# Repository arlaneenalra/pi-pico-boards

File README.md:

# pi-pico-boards
A place to keep various pi-pico-board experiments

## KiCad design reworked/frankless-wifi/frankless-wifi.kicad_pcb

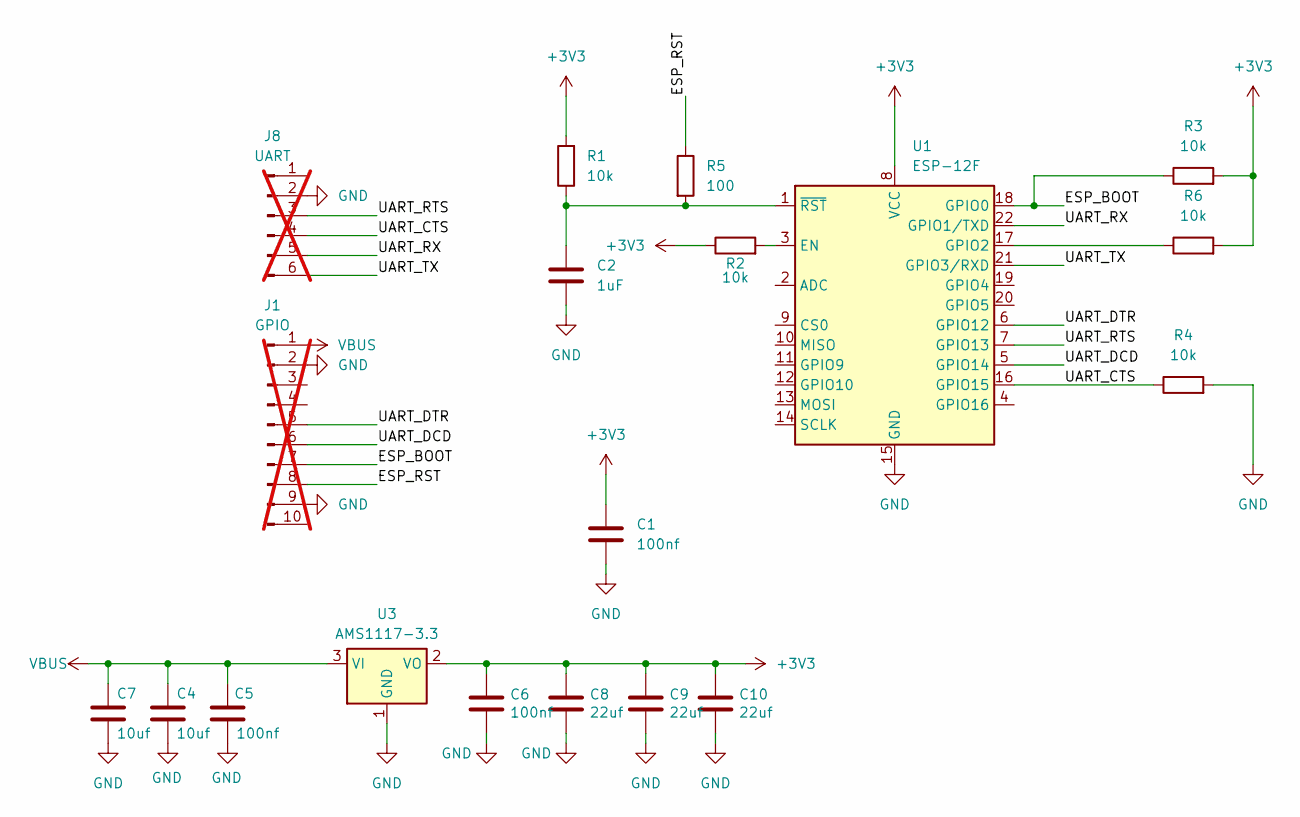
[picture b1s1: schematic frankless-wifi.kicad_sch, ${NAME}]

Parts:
C1: 100nf; C_0402_1005Metric; LCSC C1525
C2: 1uF; C_0402_1005Metric; LCSC C52923
C4, C7: 10uf; C_0603_1608Metric; LCSC Part # C96446
C5, C6: 100nf; C_0402_1005Metric; LCSC Part # C1525
C8, C9, C10: 22uf; C_0603_1608Metric; LCSC Part # C59461
J1: GPIO; PinHeader_2x05_P2.54mm_Vertical; not fitted
J8: UART; PinHeader_2x03_P2.54mm_Vertical; not fitted
R1, R2, R3, R4, R6: 10k; R_0402_1005Metric; LCSC C25744
R5: 100; R_0402_1005Metric; LCSC C25076
U1: ESP-12F; ESP-12E
U3: AMS1117-3.3; SOT-223-3_TabPin2; LCSC Part # C6186

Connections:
+3V3: C1.1, C6.1, C8.1, C9.1, C10.1, R1.2, R2.1, R3.2, R6.2, U1.8 (VCC), U3.2 (VO)
/ESP_BOOT: J1.7, R3.1, U1.18 (GPIO0)
/ESP_RST: J1.8, R5.1
/UART_CTS: J8.4, R4.1, U1.16 (GPIO15)
/UART_DCD: J1.6, U1.5 (GPIO14)
/UART_DTR: J1.5, U1.6 (GPIO12)
/UART_RTS: J8.3, U1.7 (GPIO13)
/UART_RX: J8.5, U1.22 (GPIO1/TXD)
/UART_TX: J8.6, U1.21 (GPIO3/RXD)
GND: C1.2, C2.2, C4.1, C5.1, C6.2, C7.1, C8.2, C9.2, C10.2, J1.2, J1.9, J8.2, R4.2, U1.15 (GND), U3.1 (GND)
unnamed: R2.2, U1.3 (EN)
unnamed: R6.1, U1.17 (GPIO2)
unnamed: C2.1, R1.1, R5.2, U1.1 (~RST)
VBUS: C4.2, C5.2, C7.2, J1.1, U3.3 (VI)

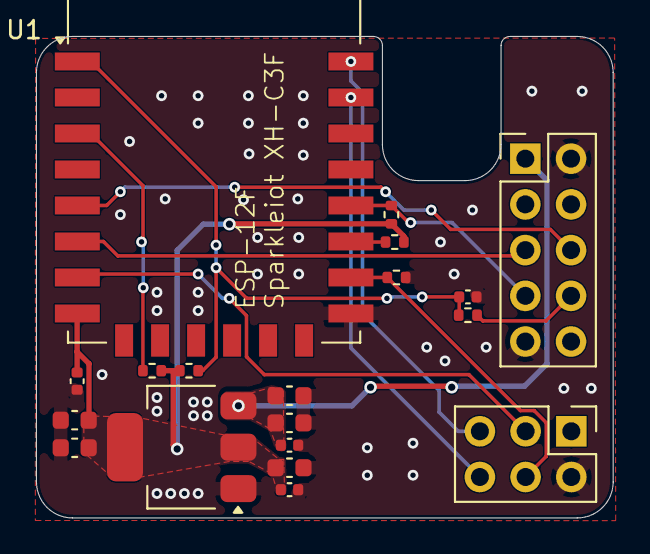
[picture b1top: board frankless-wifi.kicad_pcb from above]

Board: 2 copper layers, 32.0 x 26.8 mm, 19 parts (0 on the bottom side), 14 nets.

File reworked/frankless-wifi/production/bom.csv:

Designator,Footprint,Quantity,Value,LCSC Part #
"C1, C5, C6",0402,3,100nf,C1525
"C10, C8, C9",0603,3,22uf,C59461
C2,0402,1,1uF,C52923
"C4, C7",0603,2,10uf,C96446
"R1, R2, R3, R4, R6",0402,5,10k,C25744
R5,0402,1,100,C25076
U3,SOT-223-3_TabPin2,1,AMS1117-3.3,C6186

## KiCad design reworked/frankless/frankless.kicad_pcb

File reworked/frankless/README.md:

This is a reworked version of rh1tech's [MicroFrank](https://github.com/rh1tech/frank/tree/master/hardware/microfrank) board. I wound up stripping it down to the basically a bare PCB and reworking the layout almost from scratch. The USB Hub and several other components have been switched out to account for what JLCPCB can provide.

As the original is GPL V3, I'll license this board in particular GPL V3 as well.

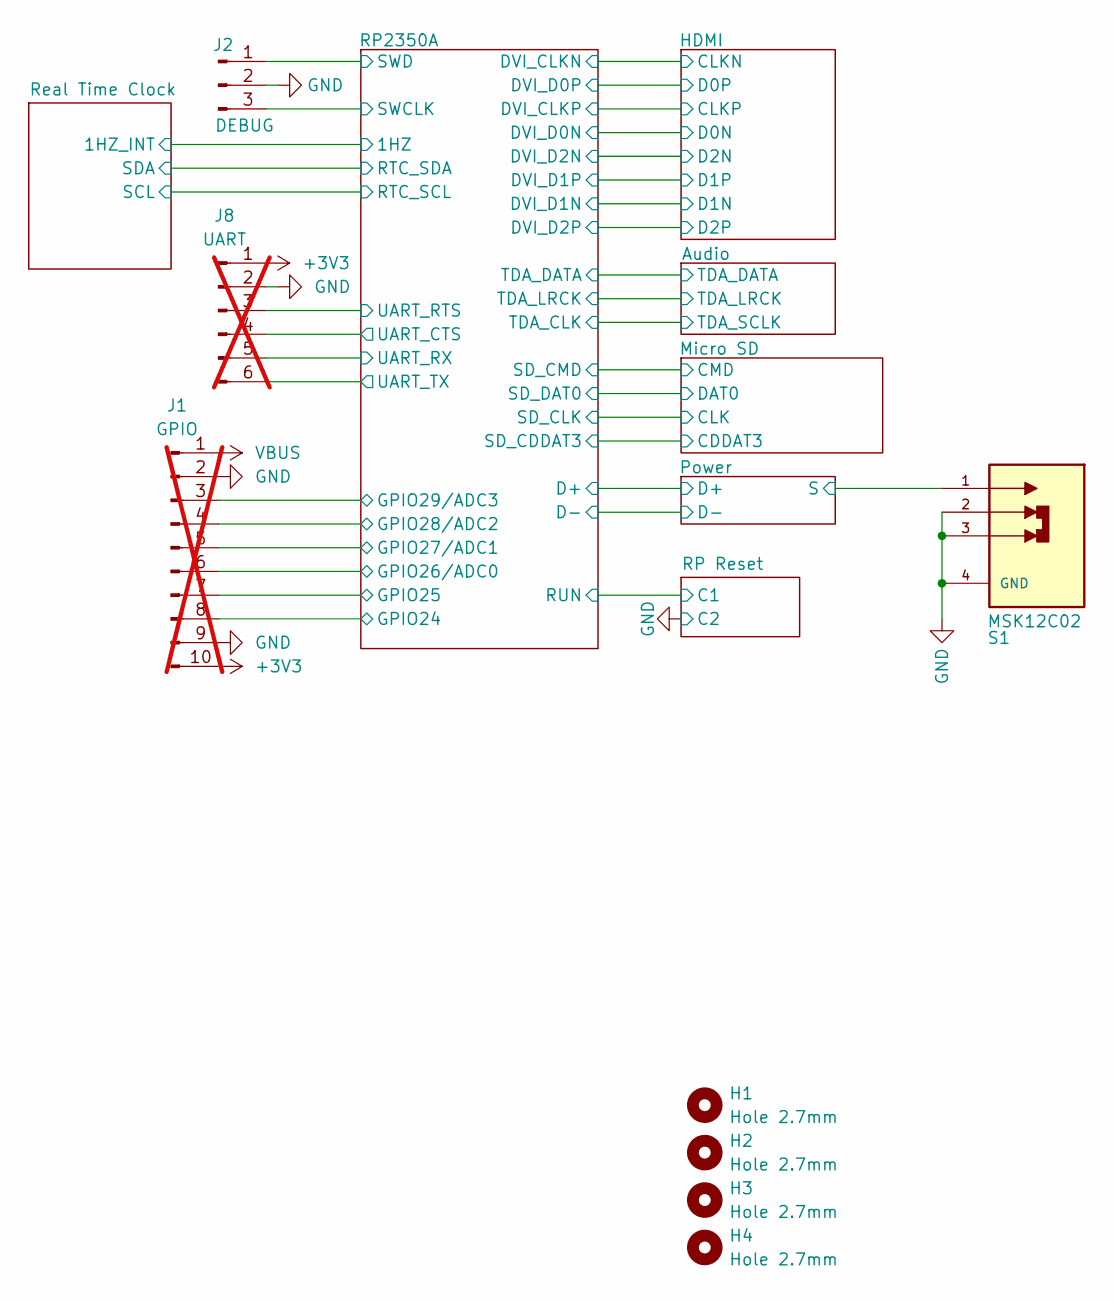
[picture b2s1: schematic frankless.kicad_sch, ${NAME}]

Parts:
H1, H2, H3, H4: Hole 2.7mm; MountingHole_2.7mm
J1: GPIO; PinHeader_2x05_P2.54mm_Vertical; not fitted
J2: DEBUG; JST_SH_1x03_P1.00mm_Vertical; LCSC Part # C160389
J8: UART; PinHeader_2x03_P2.54mm_Vertical; not fitted
S1: MSK12C02; Switch_Slide_MSK12C02; PARTREV A/0; LCSC Part # C431540

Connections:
+3V3: J1.10, J8.1; also elsewhere on the board
/Power/S: S1.1; also elsewhere on the board
/RP2350A/GPIO24: J1.8; also elsewhere on the board
/RP2350A/GPIO25: J1.7; also elsewhere on the board
/RP2350A/GPIO26/ADC0: J1.6; also elsewhere on the board
/RP2350A/GPIO27/ADC1: J1.5; also elsewhere on the board
/RP2350A/GPIO28/ADC2: J1.4; also elsewhere on the board
/RP2350A/GPIO29/ADC3: J1.3; also elsewhere on the board
/RP2350A/SWCLK: J2.3; also elsewhere on the board
/RP2350A/SWD: J2.1; also elsewhere on the board
/RP2350A/UART_CTS: J8.4; also elsewhere on the board
/RP2350A/UART_RTS: J8.3; also elsewhere on the board
/RP2350A/UART_RX: J8.5; also elsewhere on the board
/RP2350A/UART_TX: J8.6; also elsewhere on the board
GND: J1.2, J1.9, J2.2, J8.2, S1.2, S1.3, S1.4 (GND_4); also elsewhere on the board
VBUS: J1.1; also elsewhere on the board

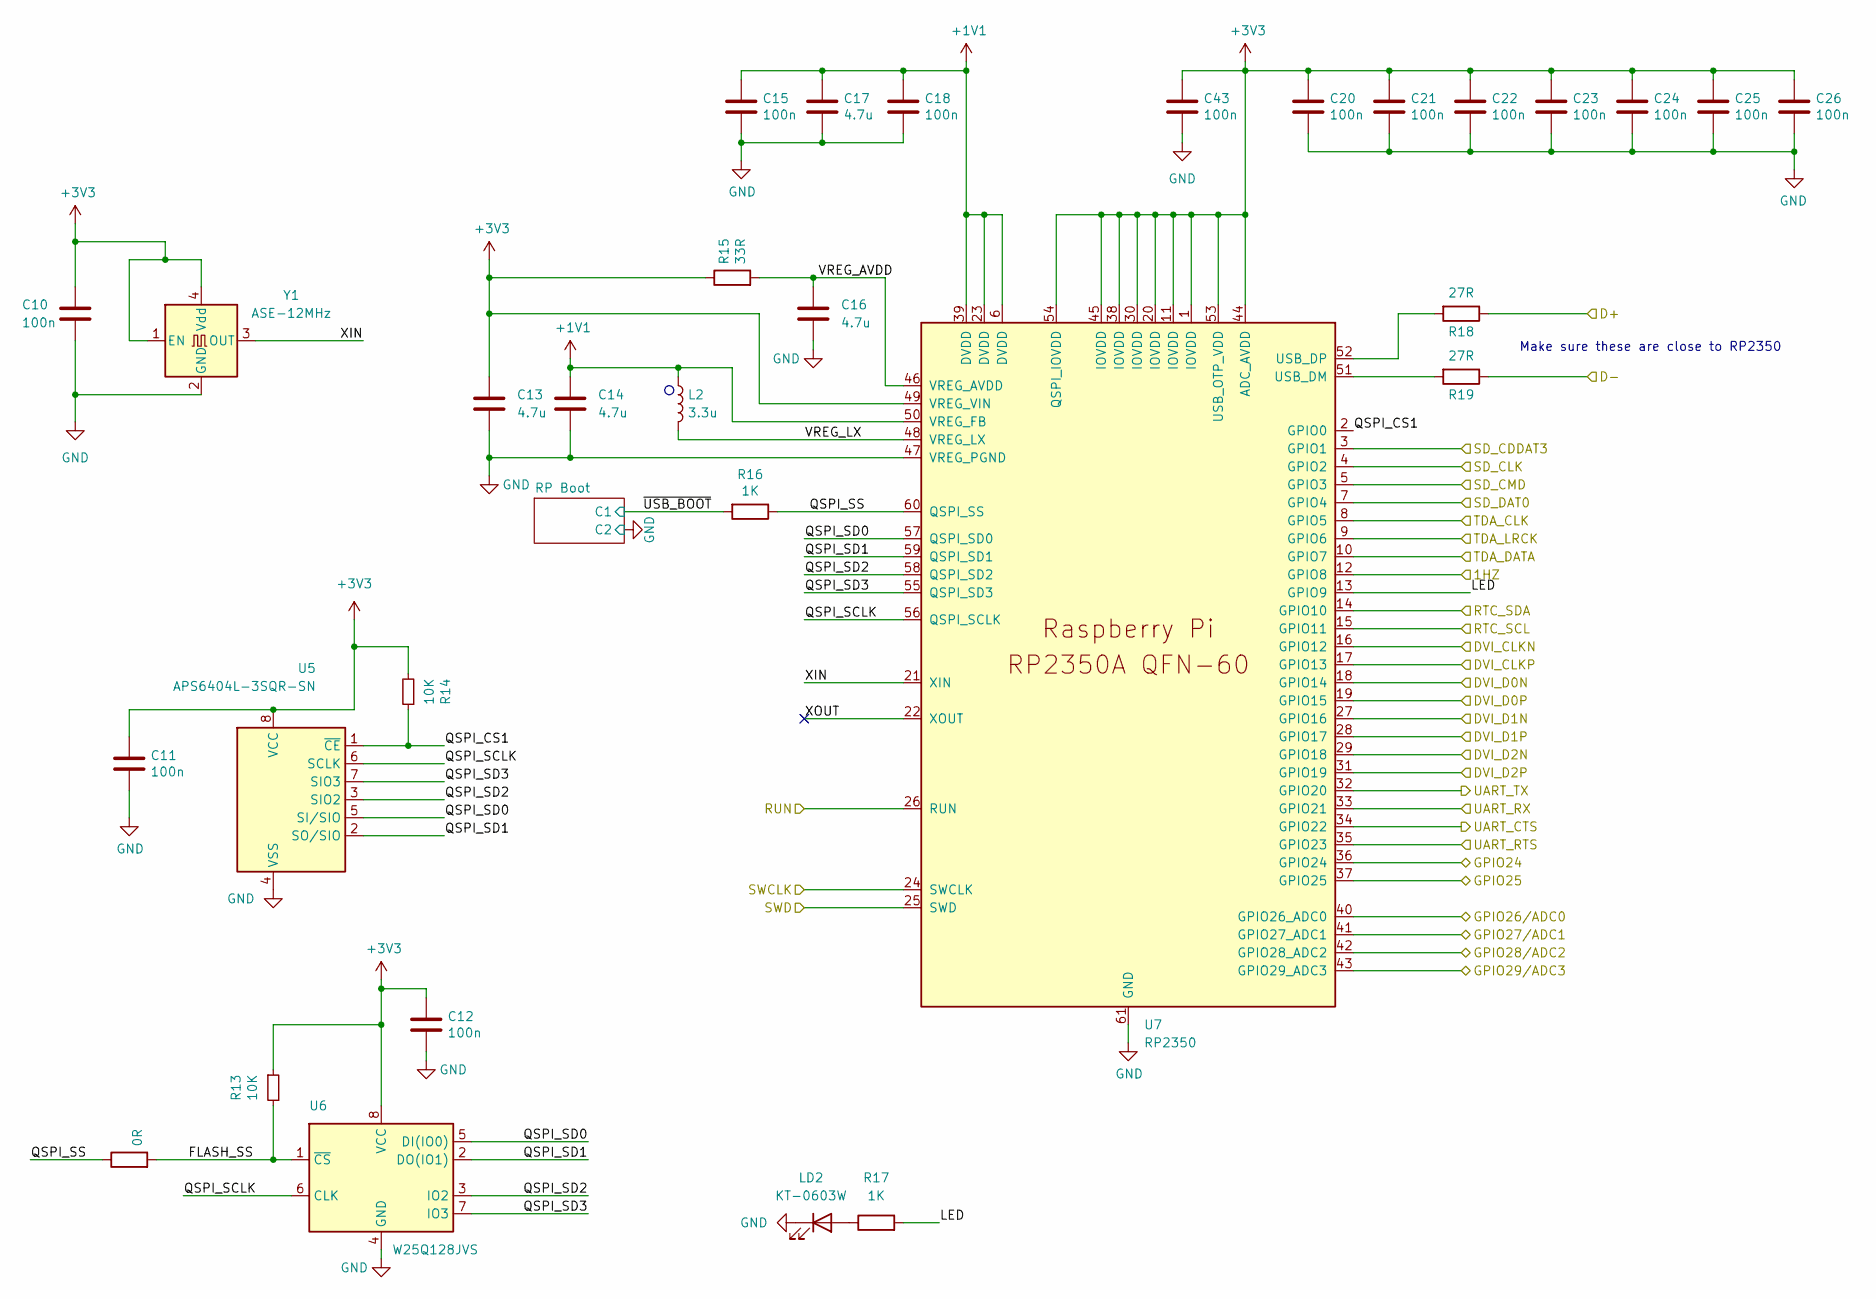
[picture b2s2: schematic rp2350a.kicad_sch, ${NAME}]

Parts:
C10, C11, C12, C15, C18, C20, C21, C22, C23, C24, C25, C26, C43: 100n; C_0402_1005Metric; LCSC Part # C1525
C13, C14: 4.7u; C_0603_1608Metric; LCSC Part # C19666
C16, C17: 4.7u; C_0402_1005Metric; LCSC Part # C2986286
L2: 3.3u; AOTA-B201610S3R3-101-T; LCSC Part # C42411119
LD2: KT-0603W; LED_0603_1608Metric; LCSC Part # C2290
R12: 0R; R_0402_1005Metric; LCSC Part # C17168
R13, R14: 10K; R_0402_1005Metric; LCSC Part # C25744
R15: 33R; R_0402_1005Metric; LCSC Part # C25105
R16, R17: 1K; R_0402_1005Metric; LCSC Part # C11702
R18, R19: 27R; R_0201_0603Metric; LCSC Part # C473051
U5: APS6404L-3SQR-SN; SOIC-8_L4.9-W3.9-P1.27-LS6.0-BL; LCSC Part # C5333729
U6: W25Q128JVS; SOIC-8; LCSC Part # C97521
U7: RP2350; QFN-60_RP2350A; LCSC Part # C42411118
Y1: ASE-12MHz; OSC-SMD_4P-L1.6-W1.2-BL; LCSC Part # C20539386

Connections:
+1V1: C14.1, C15.1, C17.1, C18.1, L2.1, U7.6 (DVDD), U7.23 (DVDD), U7.39 (DVDD), U7.50 (VREG_FB)
+3V3: C10.1, C11.1, C12.1, C13.1, C20.1, C21.1, C22.1, C23.1, C24.1, C25.1, C26.1, C43.1, R13.1, R14.2, R15.1, U5.8 (VCC), U6.8 (VCC), U7.1 (IOVDD), U7.11 (IOVDD), U7.20 (IOVDD), U7.30 (IOVDD), U7.38 (IOVDD), U7.44 (ADC_AVDD), U7.45 (IOVDD), U7.49 (VREG_VIN), U7.53 (USB_OTP_VDD), U7.54 (QSPI_IOVDD), Y1.1 (EN), Y1.4 (Vdd); also elsewhere on the board
/Audio/TDA_DATA: U7.10 (GPIO7); also elsewhere on the board
/Audio/TDA_LRCK: U7.9 (GPIO6); also elsewhere on the board
/Audio/TDA_SCLK: U7.8 (GPIO5); also elsewhere on the board
/HDMI/CLKN: U7.16 (GPIO12); also elsewhere on the board
/HDMI/CLKP: U7.17 (GPIO13); also elsewhere on the board
/HDMI/D0N: U7.18 (GPIO14); also elsewhere on the board
/HDMI/D0P: U7.19 (GPIO15); also elsewhere on the board
/HDMI/D1N: U7.27 (GPIO16); also elsewhere on the board
/HDMI/D1P: U7.28 (GPIO17); also elsewhere on the board
/HDMI/D2N: U7.29 (GPIO18); also elsewhere on the board
/HDMI/D2P: U7.31 (GPIO19); also elsewhere on the board
/Micro SD/CDDAT3: U7.3 (GPIO1); also elsewhere on the board
/Micro SD/CLK: U7.4 (GPIO2); also elsewhere on the board
/Micro SD/CMD: U7.5 (GPIO3); also elsewhere on the board
/Micro SD/DAT0: U7.7 (GPIO4); also elsewhere on the board
/Power/D+: R18.1; also elsewhere on the board
/Power/D-: R19.1; also elsewhere on the board
/RP2350A/1HZ: U7.12 (GPIO8); also elsewhere on the board
/RP2350A/FLASH_SS: R12.2, R13.2, U6.1 (~CS)
/RP2350A/GPIO24: U7.36 (GPIO24); also elsewhere on the board
/RP2350A/GPIO25: U7.37 (GPIO25); also elsewhere on the board
/RP2350A/GPIO26/ADC0: U7.40 (GPIO26_ADC0); also elsewhere on the board
/RP2350A/GPIO27/ADC1: U7.41 (GPIO27_ADC1); also elsewhere on the board
/RP2350A/GPIO28/ADC2: U7.42 (GPIO28_ADC2); also elsewhere on the board
/RP2350A/GPIO29/ADC3: U7.43 (GPIO29_ADC3); also elsewhere on the board
/RP2350A/LED: R17.2, U7.13 (GPIO9)
/RP2350A/QSPI_CS1: R14.1, U5.1 (~CE), U7.2 (GPIO0)
/RP2350A/QSPI_SCLK: U5.6 (SCLK), U6.6 (CLK), U7.56 (QSPI_SCLK)
/RP2350A/QSPI_SD0: U5.5 (SI/SIO), U6.5 (DI(IO0)), U7.57 (QSPI_SD0)
/RP2350A/QSPI_SD1: U5.2 (SO/SIO), U6.2 (DO(IO1)), U7.59 (QSPI_SD1)
/RP2350A/QSPI_SD2: U5.3 (SIO2), U6.3 (IO2), U7.58 (QSPI_SD2)
/RP2350A/QSPI_SD3: U5.7 (SIO3), U6.7 (IO3), U7.55 (QSPI_SD3)
/RP2350A/QSPI_SS: R12.1, R16.1, U7.60 (QSPI_SS)
/RP2350A/RTC_SCL: U7.15 (GPIO11); also elsewhere on the board
/RP2350A/RTC_SDA: U7.14 (GPIO10); also elsewhere on the board
/RP2350A/SWCLK: U7.24 (SWCLK); also elsewhere on the board
/RP2350A/SWD: U7.25 (SWD); also elsewhere on the board
/RP2350A/UART_CTS: U7.34 (GPIO22); also elsewhere on the board
/RP2350A/UART_RTS: U7.35 (GPIO23); also elsewhere on the board
/RP2350A/UART_RX: U7.33 (GPIO21); also elsewhere on the board
/RP2350A/UART_TX: U7.32 (GPIO20); also elsewhere on the board
/RP2350A/VREG_AVDD: C16.1, R15.2, U7.46 (VREG_AVDD)
/RP2350A/VREG_LX: L2.2, U7.48 (VREG_LX)
/RP2350A/XIN: U7.21 (XIN), Y1.3 (OUT)
/RP2350A/XOUT: U7.22 (XOUT)
/RP2350A/~USB_BOOT: R16.2; also elsewhere on the board
/RP Reset/C1: U7.26 (RUN); also elsewhere on the board
GND: C10.2, C11.2, C12.2, C13.2, C14.2, C15.2, C16.2, C17.2, C18.2, C20.2, C21.2, C22.2, C23.2, C24.2, C25.2, C26.2, C43.2, LD2.1 (K), U5.4 (VSS), U6.4 (GND), U7.47 (VREG_PGND), U7.61 (GND), Y1.2 (GND); also elsewhere on the board
unnamed: LD2.2 (A), R17.1
unnamed: R19.2, U7.51 (USB_DM)
unnamed: R18.2, U7.52 (USB_DP)

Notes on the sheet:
Make sure these are close to RP2350

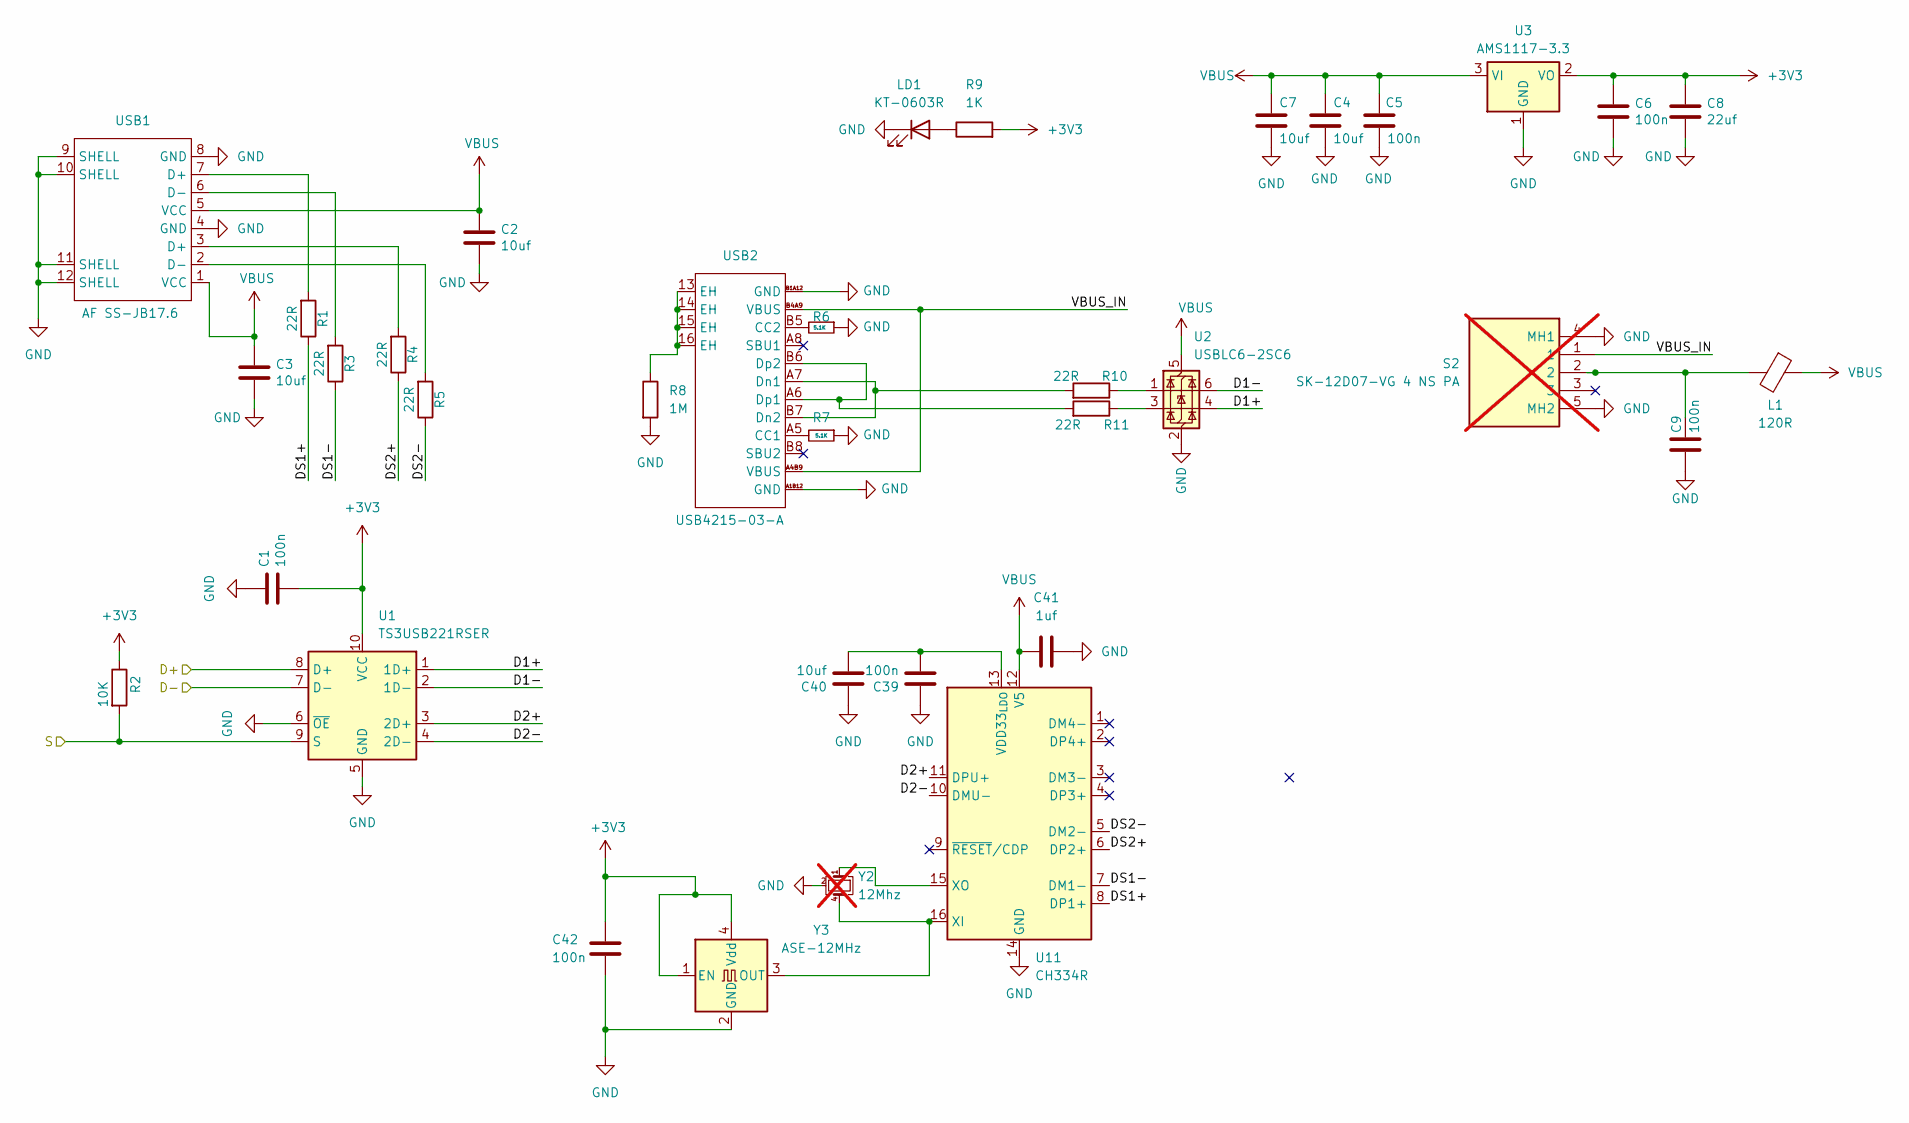
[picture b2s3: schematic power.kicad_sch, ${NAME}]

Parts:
C1, C5, C6, C9, C39, C42: 100n; C_0402_1005Metric; LCSC Part # C1525
C2, C3, C40: 10uf; C_0402_1005Metric; LCSC Part # C77000
C4, C7: 10uf; C_0603_1608Metric; LCSC Part # C96446
C8: 22uf; C_0603_1608Metric; LCSC Part # C59461
C41: 1uf; C_0402_1005Metric; LCSC Part # C14445
L1: 120R; L_0603_1608Metric; LCSC Part # C14709
LD1: KT-0603R; LED_0603_1608Metric; LCSC Part # C2286
R1, R3, R4, R5, R10, R11: 22R; R_0402_1005Metric; LCSC Part # C25092
R2: 10K; R_0402_1005Metric; LCSC Part # C25744
R6, R7: 5.1K; R_0402_1005Metric; LCSC Part # C25905
R8: 1M; R_0402_1005Metric; LCSC Part # C26083
R9: 1K; R_0402_1005Metric; LCSC Part # C11702
S2: SK-12D07-VG 4 NS PA; Switch_Slide_SK12D07VG3NS; Mouser Part Number 611-SK12D07VG3NS; not fitted
U1: TS3USB221RSER; UQFN-10; LCSC Part # C130085
U2: USBLC6-2SC6; SOT-23-6; LCSC Part # C2687116
U3: AMS1117-3.3; SOT-223-3_TabPin2; LCSC Part # C6186
U11: CH334R; QSOP-16_3.9x4.9mm_P0.635mm; LCSC Part # C4154405
USB1: AF SS-JB17.6; USB-A-TH_AF-SS-JB17.6; Manufacturer Part AF SS-JB17.6; LCSC Part Name Type-A 母 弯插
USB2: USB4215-03-A; USB-C-SMD_GT-USB-7010B; Manufacturer Part USB4215-03-A; LCSC Part Name Type-C 母
Y2: 12Mhz; CRYSTAL-SMD_4P-L3.2-W2.5-BL; LCSC Part # C9002; not fitted
Y3: ASE-12MHz; OSC-SMD_4P-L1.6-W1.2-BL; LCSC Part # C20539386

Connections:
+3V3: C1.2, C6.1, C8.1, C42.1, R2.1, R9.2, U1.10 (VCC), U3.2 (VO), Y3.1 (EN), Y3.4 (Vdd); also elsewhere on the board
/Power/D1+: U1.1 (1D+), U2.4 (I/O2)
/Power/D1-: U1.2 (1D-), U2.6 (I/O1)
/Power/D2+: U1.3 (2D+), U11.11 (DPU+)
/Power/D2-: U1.4 (2D-), U11.10 (DMU-)
/Power/D+: U1.8 (D+); also elsewhere on the board
/Power/D-: U1.7 (D-); also elsewhere on the board
/Power/DS1+: R1.1, U11.8 (DP1+)
/Power/DS1-: R3.1, U11.7 (DM1-)
/Power/DS2+: R4.1, U11.6 (DP2+)
/Power/DS2-: R5.1, U11.5 (DM2-)
/Power/S: R2.2, U1.9 (S); also elsewhere on the board
/Power/VBUS_IN: S2.1, USB2.A4B9 (VBUS), USB2.B4A9 (VBUS)
GND: C1.1, C2.2, C3.2, C4.1, C5.1, C6.2, C7.1, C8.2, C9.2, C39.1, C40.1, C41.2, C42.2, LD1.1 (K), R6.1, R7.1, R8.2, S2.4 (MH1), S2.5 (MH2), U1.5 (GND), U1.6 (~OE), U2.2 (GND), U3.1 (GND), U11.14 (GND), USB1.4 (GND), USB1.8 (GND), USB1.9 (SHELL), USB1.10 (SHELL), USB1.11 (SHELL), USB1.12 (SHELL), USB2.A1B12 (GND), USB2.B1A12 (GND), Y2.2 (G), Y2.3 (G), Y3.2 (GND); also elsewhere on the board
unnamed: C9.1, L1.2, S2.2
unnamed: LD1.2 (A), R9.1
unnamed: R1.2, USB1.7 (D+)
unnamed: R3.2, USB1.6 (D-)
unnamed: R4.2, USB1.3 (D+)
unnamed: R5.2, USB1.2 (D-)
unnamed: R8.1, USB2.13 (EH), USB2.14 (EH), USB2.15 (EH), USB2.16 (EH)
unnamed: R10.1, U2.1 (I/O1)
unnamed: R11.1, U2.3 (I/O2)
unnamed: C39.2, C40.2, U11.13 (VDD33_{LDO})
unnamed: U11.16 (XI), Y2.4, Y3.3 (OUT)
unnamed: U11.15 (XO), Y2.1
unnamed: R7.2, USB2.A5 (CC1)
unnamed: R6.2, USB2.B5 (CC2)
unnamed: R10.2, USB2.A7 (Dn1), USB2.B7 (Dn2)
unnamed: R11.2, USB2.A6 (Dp1), USB2.B6 (Dp2)
VBUS: C2.1, C3.1, C4.2, C5.2, C7.2, C41.1, L1.1, U2.5 (VBUS), U3.3 (VI), U11.12 (V5), USB1.1 (VCC), USB1.5 (VCC); also elsewhere on the board

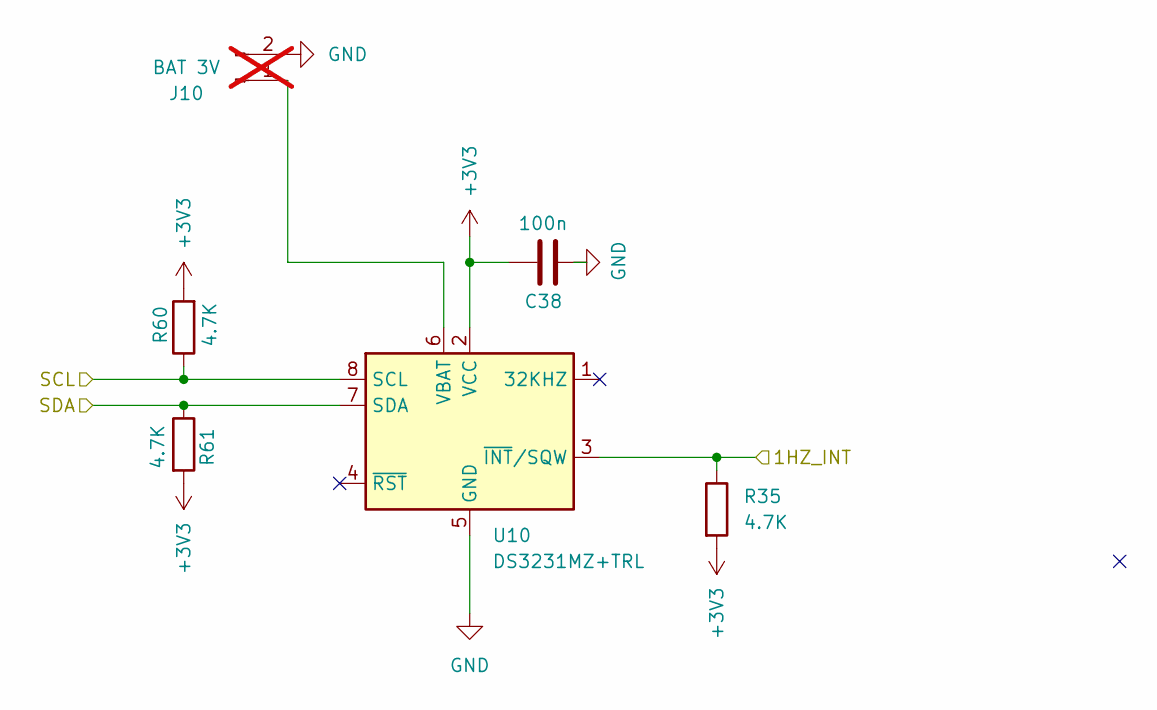
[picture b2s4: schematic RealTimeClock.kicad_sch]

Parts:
C38: 100n; C_0402_1005Metric; LCSC Part # C1525
J10: BAT 3V; PinHeader_1x02_P2.54mm_Vertical; not fitted
R35, R60, R61: 4.7K; R_0402_1005Metric; LCSC Part # C25900
U10: DS3231MZ+TRL; SOIC-8_3.9x4.9mm_P1.27mm; LCSC Part # C107410

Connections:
+3V3: C38.1, R35.2, R60.2, R61.2, U10.2 (VCC); also elsewhere on the board
/RP2350A/1HZ: R35.1, U10.3 (~INT/SQW); also elsewhere on the board
/RP2350A/RTC_SCL: R60.1, U10.8 (SCL); also elsewhere on the board
/RP2350A/RTC_SDA: R61.1, U10.7 (SDA); also elsewhere on the board
GND: C38.2, J10.2, U10.5 (GND); also elsewhere on the board
unnamed: J10.1, U10.6 (VBAT)

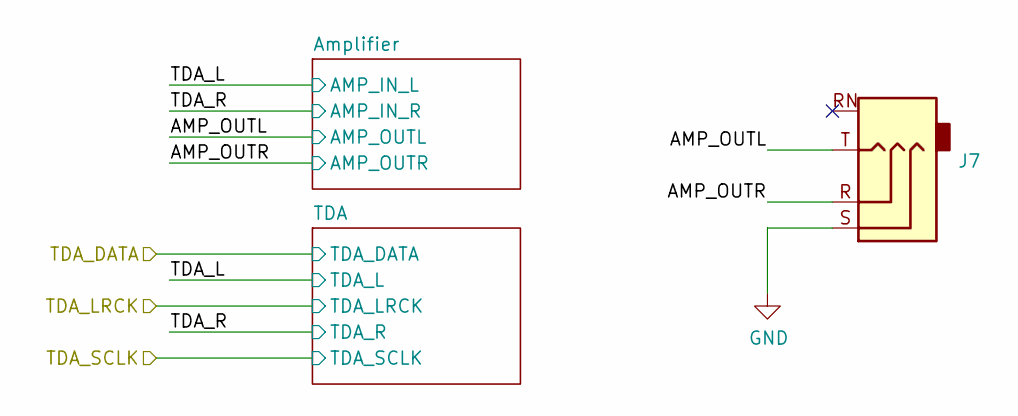
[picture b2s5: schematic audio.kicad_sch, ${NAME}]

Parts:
J7: PJ-320D; AudioJack_3.5mm_PJ320D; LCSC Part # C431535

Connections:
/Audio/AMP_OUTL: J7.T; also elsewhere on the board
/Audio/AMP_OUTR: J7.R; also elsewhere on the board
GND: J7.S; also elsewhere on the board

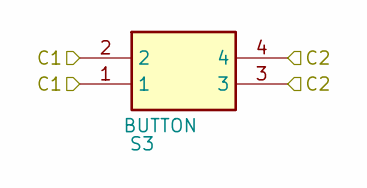
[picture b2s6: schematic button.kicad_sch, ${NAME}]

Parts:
S3: BUTTON; SW-SMD_4P-L3.5-W3.0-P1.50-LS4.7; Mouser Part Number 611-KMR221G-LFS

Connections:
/RP Reset/C1: S3.1, S3.2; also elsewhere on the board
GND: S3.3, S3.4; also elsewhere on the board

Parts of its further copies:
S4: BUTTON; SW-SMD_4P-L3.5-W3.0-P1.50-LS4.7; Mouser Part Number 611-KMR221G-LFS

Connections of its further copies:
/RP2350A/~USB_BOOT: S4.1, S4.2; also elsewhere on the board
GND: S4.3, S4.4; also elsewhere on the board

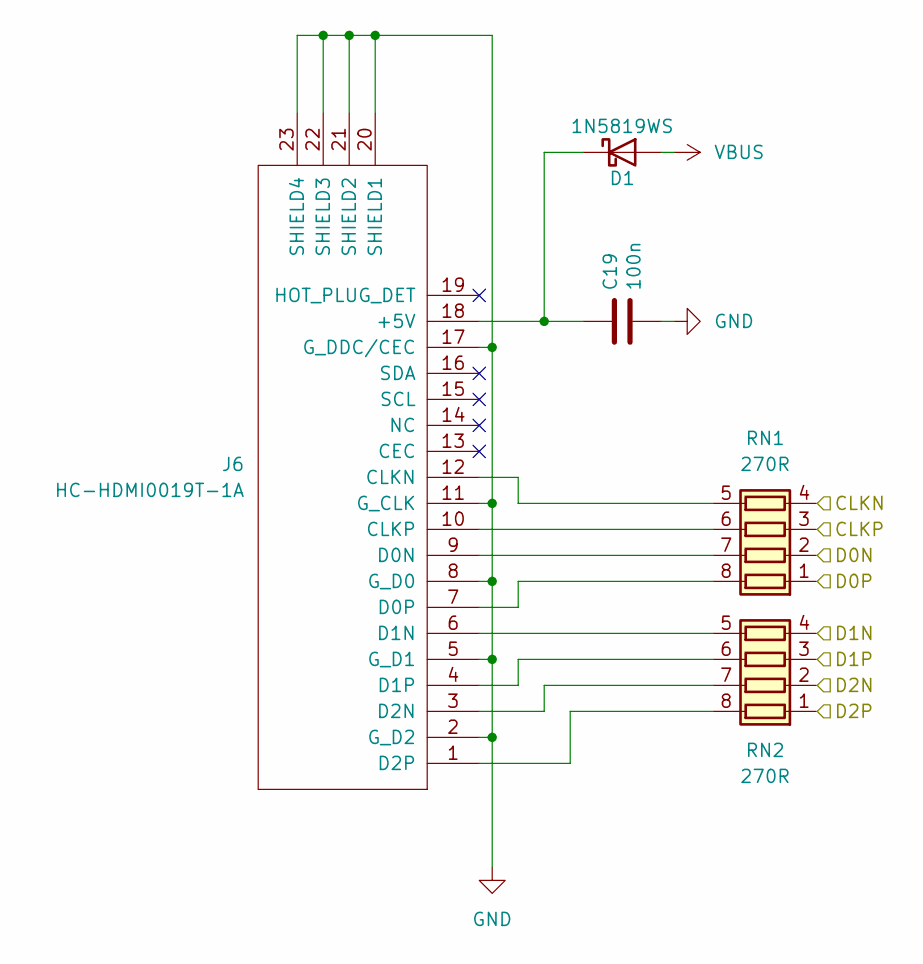
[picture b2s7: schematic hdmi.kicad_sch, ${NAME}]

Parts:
C19: 100n; C_0402_1005Metric; LCSC Part # C1525
D1: 1N5819WS; D_SOD-323; LCSC Part # C191023
J6: HC-HDMI0019T-1A; HDMI-SMD_HC-HDMI0019T-2; LCSC Part # C51927036
RN1, RN2: 270R; R_Array_Convex_4x0402; LCSC Part # C728722

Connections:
/HDMI/CLKN: RN1.4 (R4.1); also elsewhere on the board
/HDMI/CLKP: RN1.3 (R3.1); also elsewhere on the board
/HDMI/D0N: RN1.2 (R2.1); also elsewhere on the board
/HDMI/D0P: RN1.1 (R1.1); also elsewhere on the board
/HDMI/D1N: RN2.4 (R4.1); also elsewhere on the board
/HDMI/D1P: RN2.3 (R3.1); also elsewhere on the board
/HDMI/D2N: RN2.2 (R2.1); also elsewhere on the board
/HDMI/D2P: RN2.1 (R1.1); also elsewhere on the board
GND: C19.2, J6.2 (G_D2), J6.5 (G_D1), J6.8 (G_D0), J6.11 (G_CLK), J6.17 (G_DDC/CEC), J6.20 (SHIELD1), J6.21 (SHIELD2), J6.22 (SHIELD3), J6.23 (SHIELD4); also elsewhere on the board
unnamed: C19.1, D1.1 (K), J6.18 (+5V)
unnamed: J6.12 (CLKN), RN1.5 (R4.2)
unnamed: J6.10 (CLKP), RN1.6 (R3.2)
unnamed: J6.9 (D0N), RN1.7 (R2.2)
unnamed: J6.7 (D0P), RN1.8 (R1.2)
unnamed: J6.6 (D1N), RN2.5 (R4.2)
unnamed: J6.4 (D1P), RN2.6 (R3.2)
unnamed: J6.3 (D2N), RN2.7 (R2.2)
unnamed: J6.1 (D2P), RN2.8 (R1.2)
VBUS: D1.2 (A); also elsewhere on the board

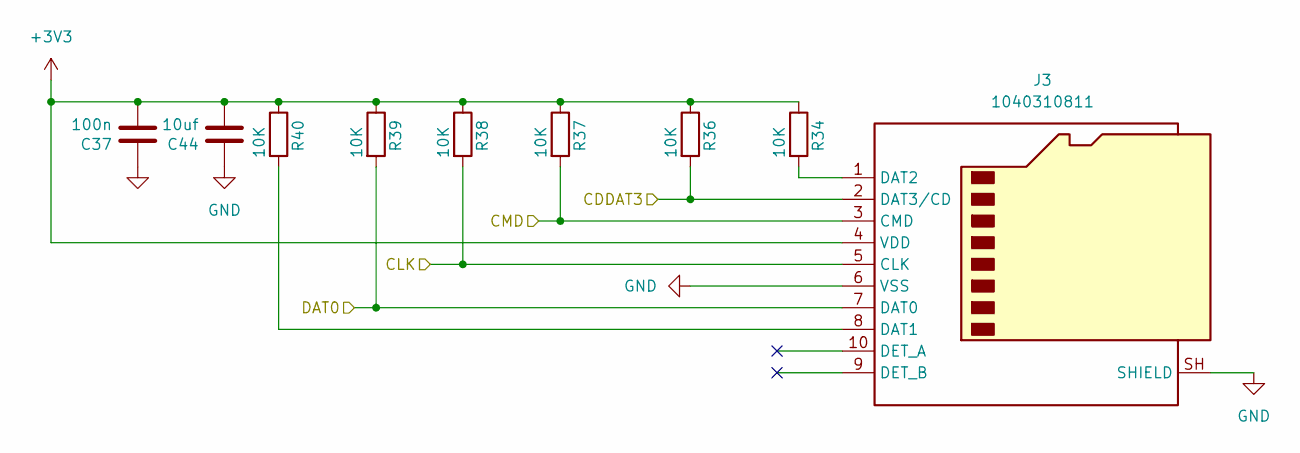
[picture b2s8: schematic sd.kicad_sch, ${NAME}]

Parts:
C37: 100n; C_0402_1005Metric; LCSC Part # C1525
C44: 10uf; C_0402_1005Metric; LCSC Part # C77000
J3: 1040310811; microSD_HC_Molex_104031-0811; LCSC Part # C585350
R34, R36, R37, R38, R39, R40: 10K; R_0402_1005Metric; LCSC Part # C25744

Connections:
+3V3: C37.2, C44.2, J3.4 (VDD), R34.1, R36.1, R37.1, R38.1, R39.1, R40.1; also elsewhere on the board
/Micro SD/CDDAT3: J3.2 (DAT3/CD), R36.2; also elsewhere on the board
/Micro SD/CLK: J3.5 (CLK), R38.2; also elsewhere on the board
/Micro SD/CMD: J3.3 (CMD), R37.2; also elsewhere on the board
/Micro SD/DAT0: J3.7 (DAT0), R39.2; also elsewhere on the board
GND: C37.1, C44.1, J3.6 (VSS), J3.SH (SHIELD); also elsewhere on the board
unnamed: J3.8 (DAT1), R40.2
unnamed: J3.1 (DAT2), R34.2

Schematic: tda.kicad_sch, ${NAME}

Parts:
C27, C29: 10uf; C_0402_1005Metric; LCSC Part # C77000
C28: 100n; C_0402_1005Metric; LCSC Part # C1525
R20: 100R; R_0402_1005Metric; LCSC Part # C25076
R21, R22: 470R; R_0402_1005Metric; LCSC Part # C25117
U8: TDA1387T; SO-8; not fitted

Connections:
/Audio/TDA_DATA: U8.3 (DATA); also elsewhere on the board
/Audio/TDA_L: R22.2, U8.6 (A_LEFT); also elsewhere on the board
/Audio/TDA_LRCK: U8.2 (LRCK); also elsewhere on the board
/Audio/TDA_R: R21.1, U8.8 (A_RIGHT); also elsewhere on the board
/Audio/TDA_SCLK: U8.1 (SCLK); also elsewhere on the board
GND: C27.2, C28.2, C29.2, R21.2, R22.1, U8.4 (AGND); also elsewhere on the board
unnamed: C29.1, U8.7 (FLT)
unnamed: C27.1, C28.1, R20.1, U8.5 (VA)
VBUS: R20.2; also elsewhere on the board

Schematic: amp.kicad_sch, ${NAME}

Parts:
C30, C31, C32, C34, C35: 10uf; C_0402_1005Metric; LCSC Part # C77000
C33: 10uf tantulum; CP_EIA-3216-18_Kemet-A; LCSC Part # C7171
C36: 100n; C_0402_1005Metric; LCSC Part # C1525
R23, R24, R25, R26, R27, R28: 10K; R_0402_1005Metric; LCSC Part # C25744
R29, R30: 47K; R_0402_1005Metric; LCSC Part # C25792
R31, R32: 20K; R_0402_1005Metric; LCSC Part # C25765
R33: 100R; R_0402_1005Metric; LCSC Part # C25076
U9: LM358; SO-8; LCSC Part # C7950

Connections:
/Audio/AMP_OUTL: C34.2, R31.2; also elsewhere on the board
/Audio/AMP_OUTR: C35.2, R32.2; also elsewhere on the board
/Audio/TDA_L: C30.1, R23.1; also elsewhere on the board
/Audio/TDA_R: C31.1, R24.1; also elsewhere on the board
GND: C32.1, C33.2, C36.1, R23.2, R24.2, R26.1, R31.1, R32.1, U9.4 (V-); also elsewhere on the board
unnamed: C30.2, R27.2
unnamed: C31.2, R28.2
unnamed: C34.1, R29.1, U9.7
unnamed: C35.1, R30.1, U9.1
unnamed: C32.2, R25.1, R26.2, U9.3 (+), U9.5 (+)
unnamed: R28.1, R30.2, U9.2 (-)
unnamed: R27.1, R29.2, U9.6 (-)
unnamed: C33.1, C36.2, R25.2, R33.2, U9.8 (V+)
VBUS: R33.1; also elsewhere on the board

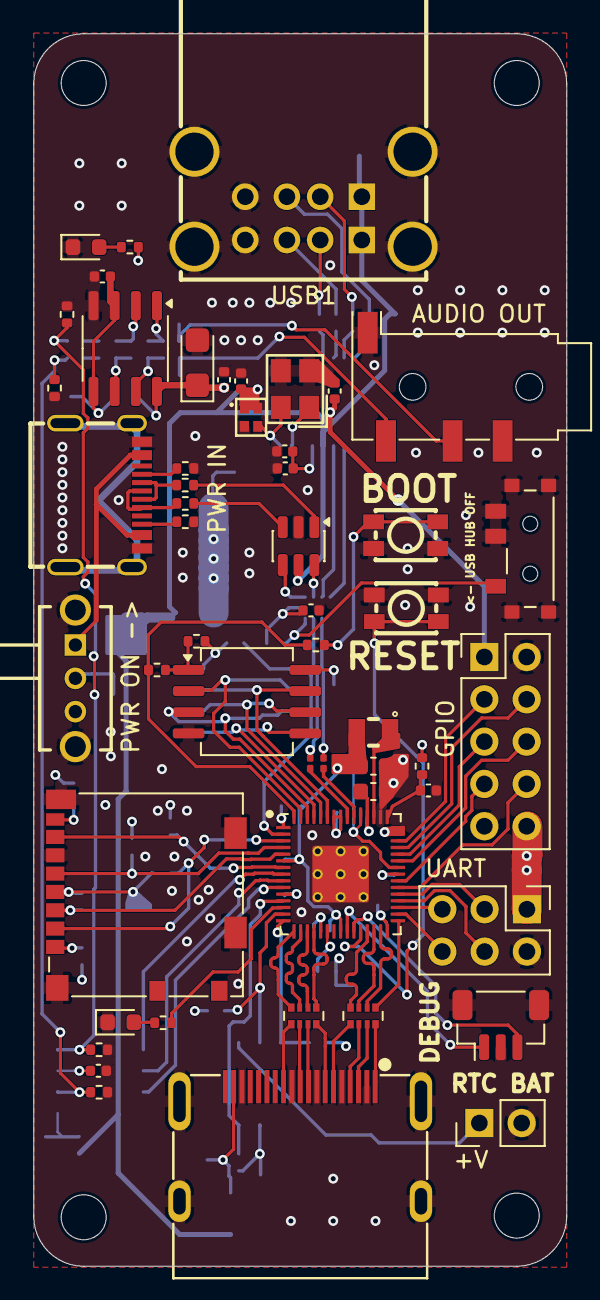
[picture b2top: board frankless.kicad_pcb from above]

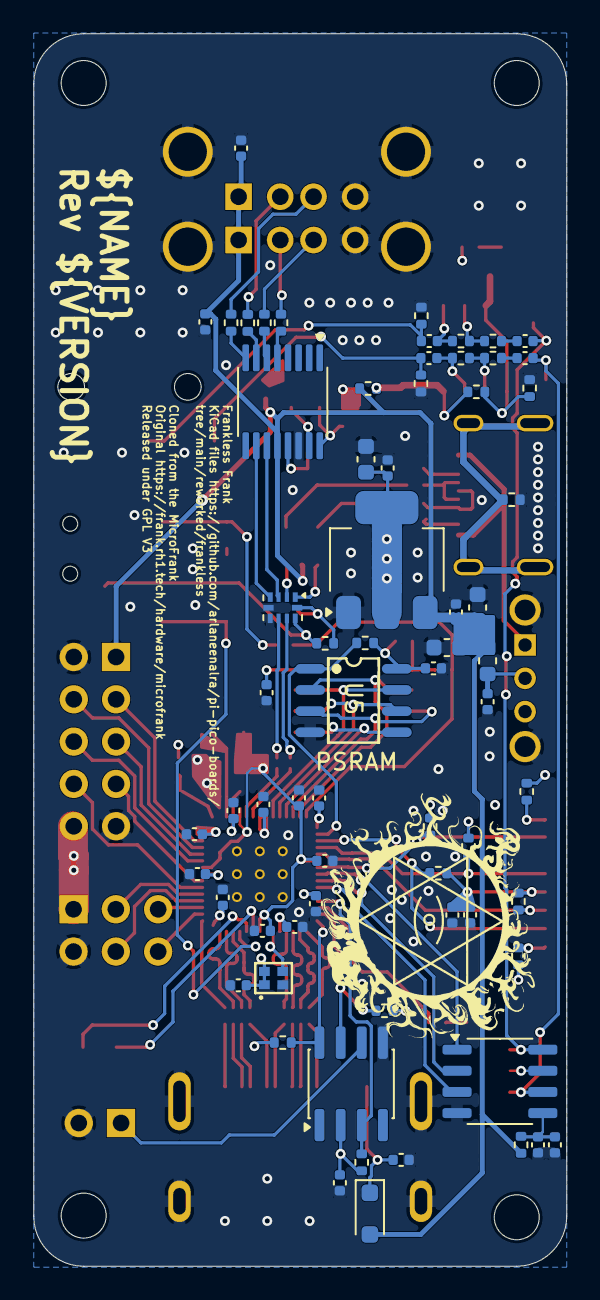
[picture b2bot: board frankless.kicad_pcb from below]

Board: 4 copper layers, 32.0 x 74.0 mm, 123 parts (67 on the bottom side), 105 nets.

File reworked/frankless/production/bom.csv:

Designator,Footprint,Quantity,Value,LCSC Part #
"C1, C10, C11, C12, C15, C18, C19, C20, C21, C22, C23, C24, C25, C26, C28, C36, C37, C38, C39, C42, C43, C5, C6, C9",0402,24,100n,C1525
"C13, C14",0603,2,4.7u,C19666
"C16, C17",0402,2,4.7u,C2986286
"C2, C27, C29, C3, C30, C31, C32, C34, C35, C40, C44",0402,11,10uf,C77000
C33,CP_EIA-3216-18_Kemet-A,1,10uf tantulum,C7171
"C4, C7",0603,2,10uf,C96446
C41,0402,1,1uf,C14445
C8,0603,1,22uf,C59461
D1,D_SOD-323,1,1N5819WS,C191023
J2,JST_SH_1x03_P1.00mm_Vertical,1,DEBUG,C160389
J3,microSD_HC_Molex_104031-0811,1,1040310811,C585350
J6,HDMI-SMD_HC-HDMI0019T-2,1,HC-HDMI0019T-1A,C51927036
J7,AudioJack_3.5mm_PJ320D,1,PJ-320D,C431535
L1,0603,1,120R,C14709
L2,AOTA-B201610S3R3-101-T,1,3.3u,C42411119
LD1,0603,1,KT-0603R,C2286
LD2,0603,1,KT-0603W,C2290
"R1, R10, R11, R3, R4, R5",0402,6,22R,C25092
R12,0402,1,0R,C17168
"R13, R14, R2, R23, R24, R25, R26, R27, R28, R34, R36, R37, R38, R39, R40",0402,15,10K,C25744
R15,0402,1,33R,C25105
"R16, R17, R9",0402,3,1K,C11702
"R18, R19",0201,2,27R,C473051
"R20, R33",0402,2,100R,C25076
"R21, R22",0402,2,470R,C25117
"R29, R30",0402,2,47K,C25792
"R31, R32",0402,2,20K,C25765
"R35, R60, R61",0402,3,4.7K,C25900
"R6, R7",0402,2,5.1K,C25905
R8,0402,1,1M,C26083
"RN1, RN2",R_Array_Convex_4x0402,2,270R,C728722
S1,Switch_Slide_MSK12C02,1,MSK12C02,C431540
"S3, S4",SW-SMD_4P-L3.5-W3.0-P1.50-LS4.7,2,BUTTON,C49393608
U1,UQFN-10,1,TS3USB221RSER,C130085
U10,SOIC-8_3.9x4.9mm_P1.27mm,1,DS3231MZ+TRL,C107410
U11,QSOP-16_3.9x4.9mm_P0.635mm,1,CH334R,C4154405
U2,SOT-23-6,1,USBLC6-2SC6,C2687116
U3,SOT-223-3_TabPin2,1,AMS1117-3.3,C6186
U5,SOIC-8_L4.9-W3.9-P1.27-LS6.0-BL,1,APS6404L-3SQR-SN,C5333729
U6,SOIC-8,1,W25Q128JVS,C97521
U7,QFN-60_RP2350A,1,RP2350,C42411118
U9,SO-8,1,LM358,C7950
USB1,USB-A-TH_AF-SS-JB17.6,1,AF SS-JB17.6,C456021
USB2,USB-C-SMD_GT-USB-7010B,1,USB4215-03-A,C37616412
"Y1, Y3",OSC-SMD_4P-L1.6-W1.2-BL,2,ASE-12MHz,C20539386

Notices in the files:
reworked/frankless/frankless.kicad_pcb:
Released under GPL V3
